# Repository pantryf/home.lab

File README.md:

homeLab
=======

Materials for setting up a home lab

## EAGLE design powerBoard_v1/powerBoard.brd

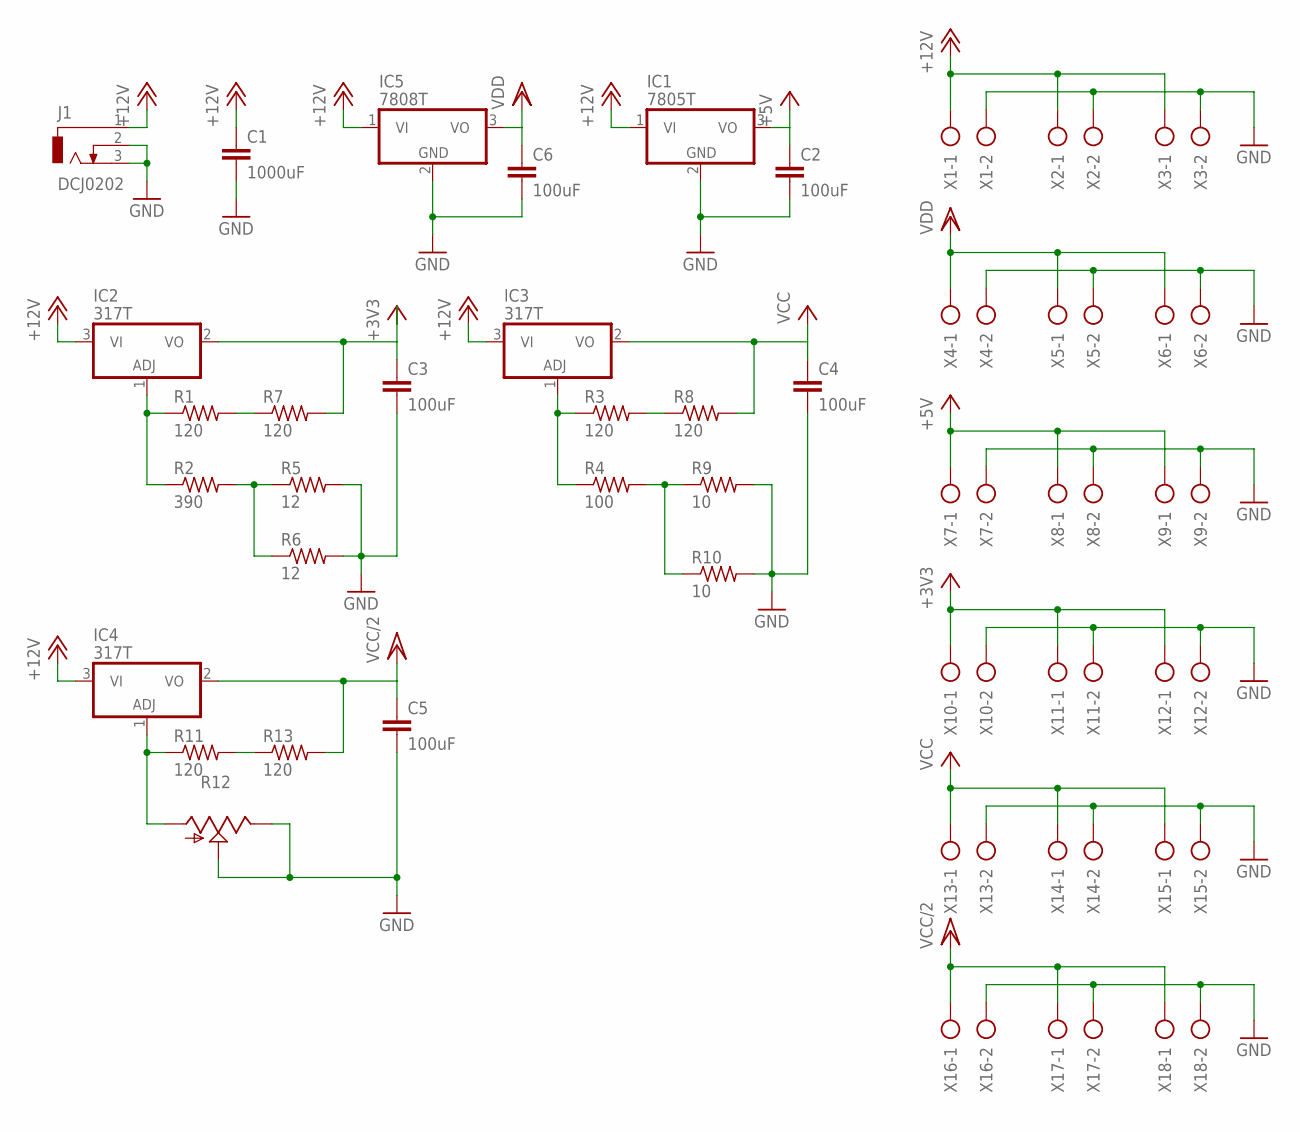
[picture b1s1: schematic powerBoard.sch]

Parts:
C1: 1000uF; C5B7.2
C2, C3, C4, C5, C6: 100uF; C5B7.2
IC1: 7805T; TO220H
IC2, IC3, IC4: 317T; TO220H
IC5: 7808T; TO220H
J1: DCJ0202
R1, R3, R7, R8, R11, R13: 120; 0207/10
R2: 390; 0207/10
R4: 100; 0207/10
R5, R6: 12; 0207/10
R9, R10: 10; 0207/10
R12: TRIM_US-RJ9W; RJ9W
X1, X2, X3, X4, X5, X6, X7, X8, X9, X10, X11, X12, X13, X14, X15, X16, X17, X18: AK300/2

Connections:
+3V3: C3.1, IC2.2 (VO), R7.2, X10.1, X11.1, X12.1
+5V: C2.1, IC1.3 (VO), X7.1, X8.1, X9.1
+12V: C1.1, IC1.1 (VI), IC2.3 (VI), IC3.3 (VI), IC4.3 (VI), IC5.1 (VI), J1.1, X1.1, X2.1, X3.1
GND: C1.2, C2.2, C3.2, C4.2, C5.2, C6.2, IC1.2 (GND), IC5.2 (GND), J1.2, J1.3, R5.2, R6.2, R9.2, R10.2, R12.E, R12.S, X1.2, X2.2, X3.2, X4.2, X5.2, X6.2, X7.2, X8.2, X9.2, X10.2, X11.2, X12.2, X13.2, X14.2, X15.2, X16.2, X17.2, X18.2
unnamed: IC2.1 (ADJ), R1.1, R2.1
unnamed: IC3.1 (ADJ), R3.1, R4.1
unnamed: R2.2, R5.1, R6.1
unnamed: R3.2, R8.1
unnamed: R1.2, R7.1
unnamed: R4.2, R9.1, R10.1
unnamed: IC4.1 (ADJ), R11.1, R12.A
unnamed: R11.2, R13.1
VCC: C4.1, IC3.2 (VO), R8.2, X13.1, X14.1, X15.1
VCC/2: C5.1, IC4.2 (VO), R13.2, X16.1, X17.1, X18.1
VDD: C6.1, IC5.3 (VO), X4.1, X5.1, X6.1

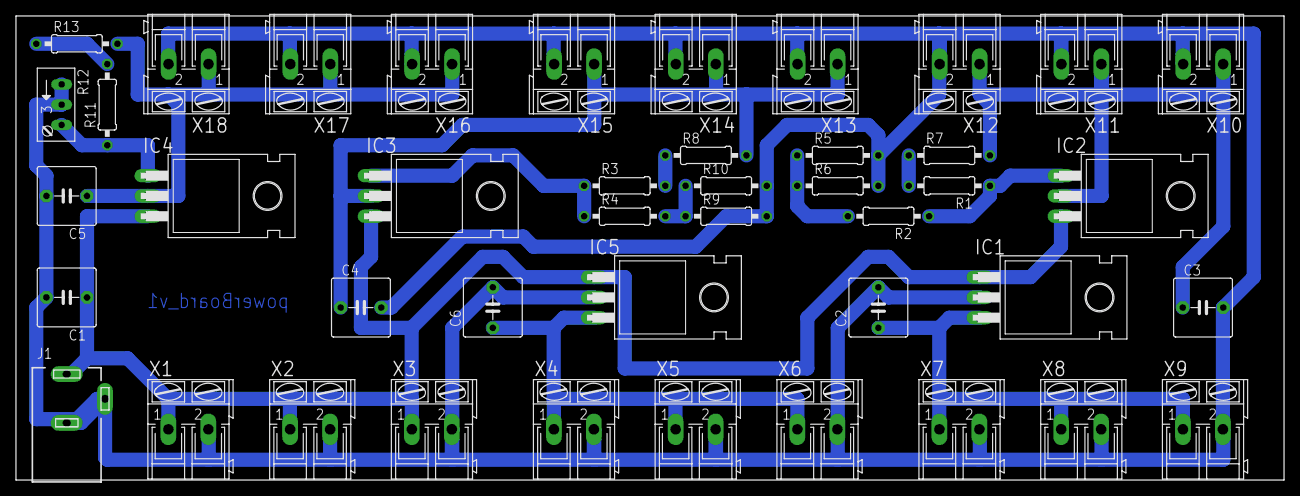
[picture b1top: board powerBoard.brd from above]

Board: 2 copper layers, 158.7 x 58.1 mm, 43 parts (0 on the bottom side), 15 nets.

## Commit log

2013-09-02 created new
2013-09-02 added powerBoard
2013-09-02 powerBoard schematic corrected
2013-09-04 board completed
2013-09-09 gerber files added
2025-04-10 :bug: with analytics (updated)
